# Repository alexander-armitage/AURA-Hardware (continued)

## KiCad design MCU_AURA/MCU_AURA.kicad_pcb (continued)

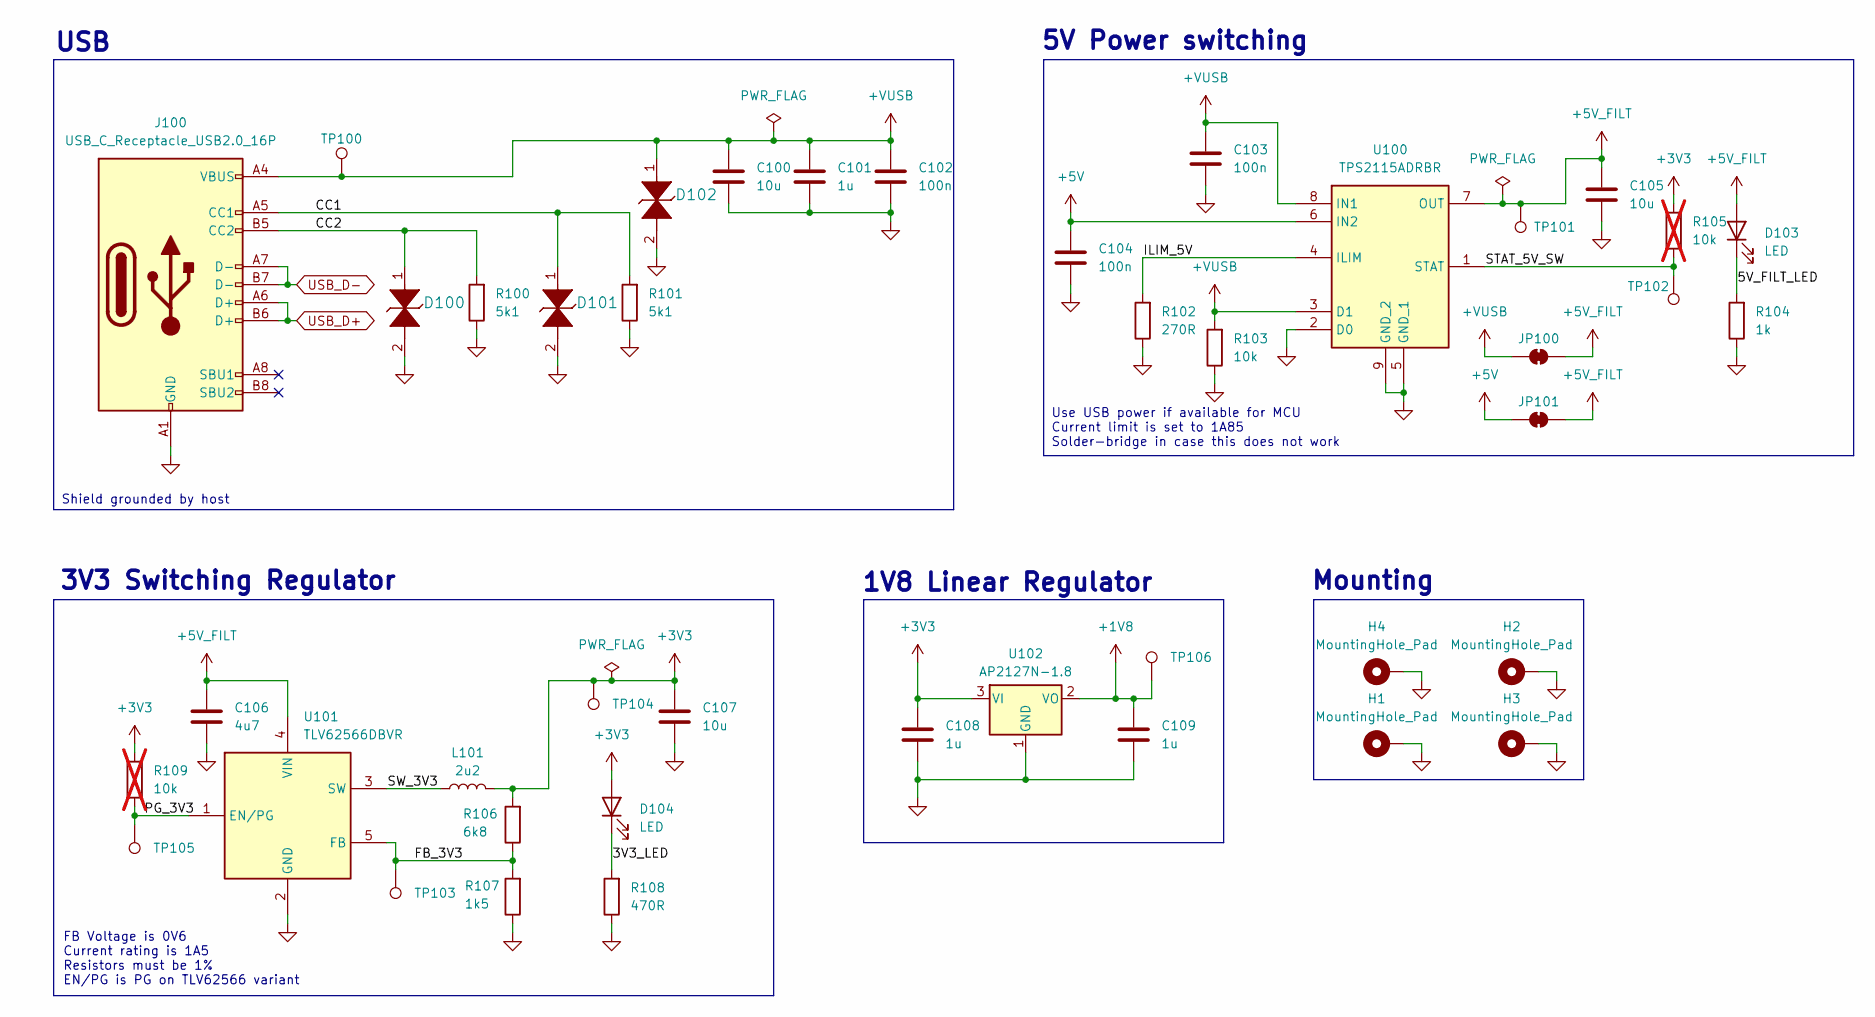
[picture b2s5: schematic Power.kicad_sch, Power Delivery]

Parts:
C100, C105, C107: 10u; C_0402_1005Metric
C101, C108, C109: 1u; C_0402_1005Metric
C102, C103, C104: 100n; C_0402_1005Metric
C106: 4u7; C_0402_1005Metric
D100, D101, D102: TPD1E05U06DPYR; DIO_TPD1E05U06DPYR
D103, D104: LED; LED_0603_1608Metric
H1, H2, H3, H4: MountingHole_Pad; MountingHole_3.2mm_M3_Pad_Via
J100: USB_C_Receptacle_USB2.0_16P; USB_C_Receptacle_GCT_USB4105-xx-A_16P_TopMnt_Horizontal
JP100, JP101: SolderJumper_2_Bridged; SolderJumper-2_P1.3mm_Open_RoundedPad1.0x1.5mm
L101: 2u2; L_1008_2520Metric
R100, R101: 5k1; R_0402_1005Metric
R102: 270R; R_0402_1005Metric
R103: 10k; R_0402_1005Metric
R104: 1k; R_0402_1005Metric
R105, R109: 10k; R_0402_1005Metric; not fitted
R106: 6k8; R_0402_1005Metric
R107: 1k5; R_0402_1005Metric
R108: 470R; R_0402_1005Metric
TP100, TP101, TP102, TP103, TP104, TP105, TP106: TestPoint; TestPoint_Pad_D1.0mm
U100: TPS2115ADRBR; SON65P300X300X100-9N-D; Manufacturer_Part_Number TPS2115ADRBR; Mouser Part Number 595-TPS2115ADRBR
U101: TLV62566DBVR; SOT95P280X145-5N; Manufacturer_Part_Number TLV62566DBVR; Mouser Part Number 595-TLV62566DBVR
U102: AP2127N-1.8; SOT-23

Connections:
+1V8: C109.1, TP106.1, U102.2 (VO); also elsewhere on the board
+3V3: C107.1, C108.1, D104.2 (A), L101.2, R105.2, R106.2, R109.2, TP104.1, U102.3 (VI); also elsewhere on the board
+5V: C104.1, JP101.1 (A), U100.6 (IN2); also elsewhere on the board
+5V_FILT: C105.1, C106.1, D103.2 (A), JP100.2 (B), JP101.2 (B), TP101.1, U100.7 (OUT), U101.4 (VIN); also elsewhere on the board
+VUSB: C100.1, C101.1, C102.1, C103.1, D102.1, J100.A4 (VBUS), J100.A9 (VBUS), J100.B4 (VBUS), J100.B9 (VBUS), JP100.1 (A), R103.2, TP100.1, U100.3 (D1), U100.8 (IN1); also elsewhere on the board
/100_Power/3V3_LED: D104.1 (K), R108.2
/100_Power/5V_FILT_LED: D103.1 (K), R104.2
/100_Power/CC1: D101.1, J100.A5 (CC1), R101.2
/100_Power/CC2: D100.1, J100.B5 (CC2), R100.2
/100_Power/FB_3V3: R106.1, R107.2, TP103.1, U101.5 (FB)
/100_Power/ILIM_5V: R102.2, U100.4 (ILIM)
/100_Power/PG_3V3: R109.1, TP105.1, U101.1 (EN/PG)
/100_Power/STAT_5V_SW: R105.1, TP102.1, U100.1 (STAT)
/100_Power/SW_3V3: L101.1, U101.3 (SW)
GND: C100.2, C101.2, C102.2, C103.2, C104.2, C105.2, C106.2, C107.2, C108.2, C109.2, D100.2, D101.2, D102.2, H1.1, H2.1, H3.1, H4.1, J100.A1 (GND), J100.A12 (GND), J100.B1 (GND), J100.B12 (GND), R100.1, R101.1, R102.1, R103.1, R104.1, R107.1, R108.1, U100.2 (D0), U100.5 (GND_1), U100.9 (GND_2), U101.2 (GND), U102.1 (GND); also elsewhere on the board
USB_D+: J100.A6 (D+), J100.B6 (D+); also elsewhere on the board
USB_D-: J100.A7 (D-), J100.B7 (D-); also elsewhere on the board

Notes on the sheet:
Mounting
Use USB power if available for MCU Current limit is set to 1A85 Solder-bridge in case this does not work
1V8 Linear Regulator
USB
Shield grounded by host
3V3 Switching Regulator
5V Power switching
FB Voltage is 0V6 Current rating is 1A5 Resistors must be 1% EN/PG is PG on TLV62566 variant

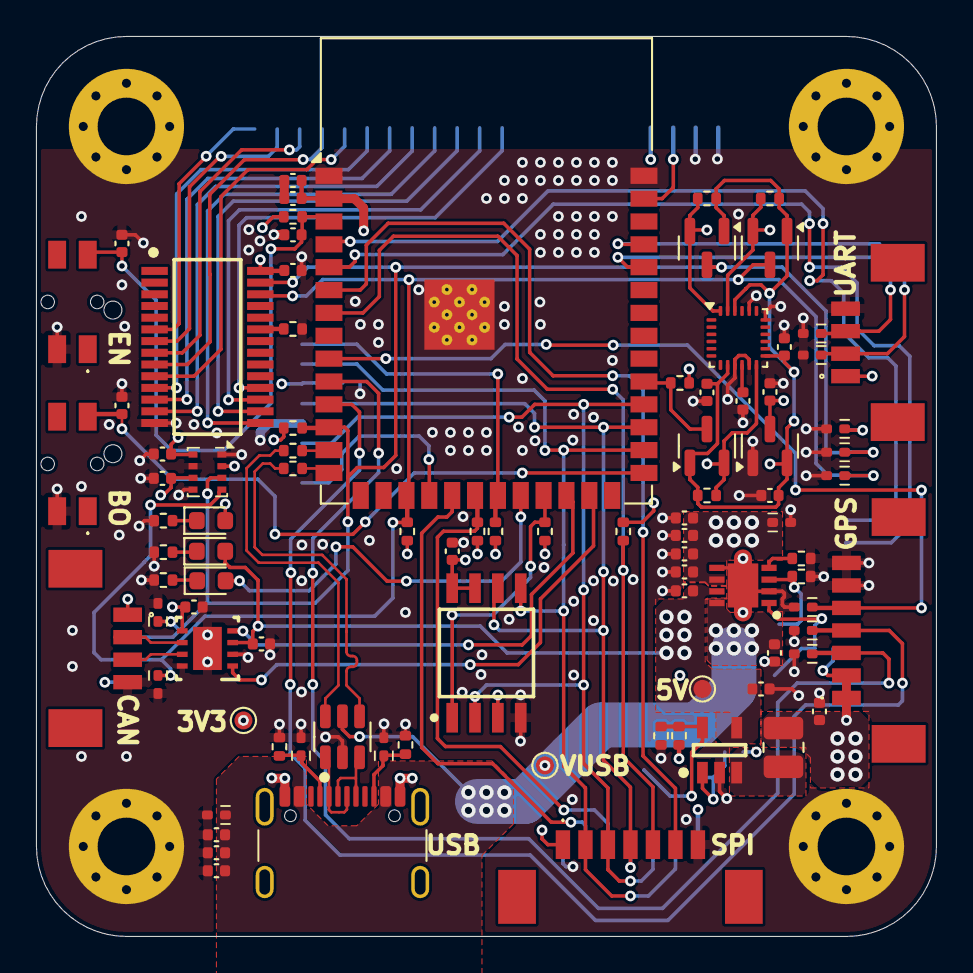
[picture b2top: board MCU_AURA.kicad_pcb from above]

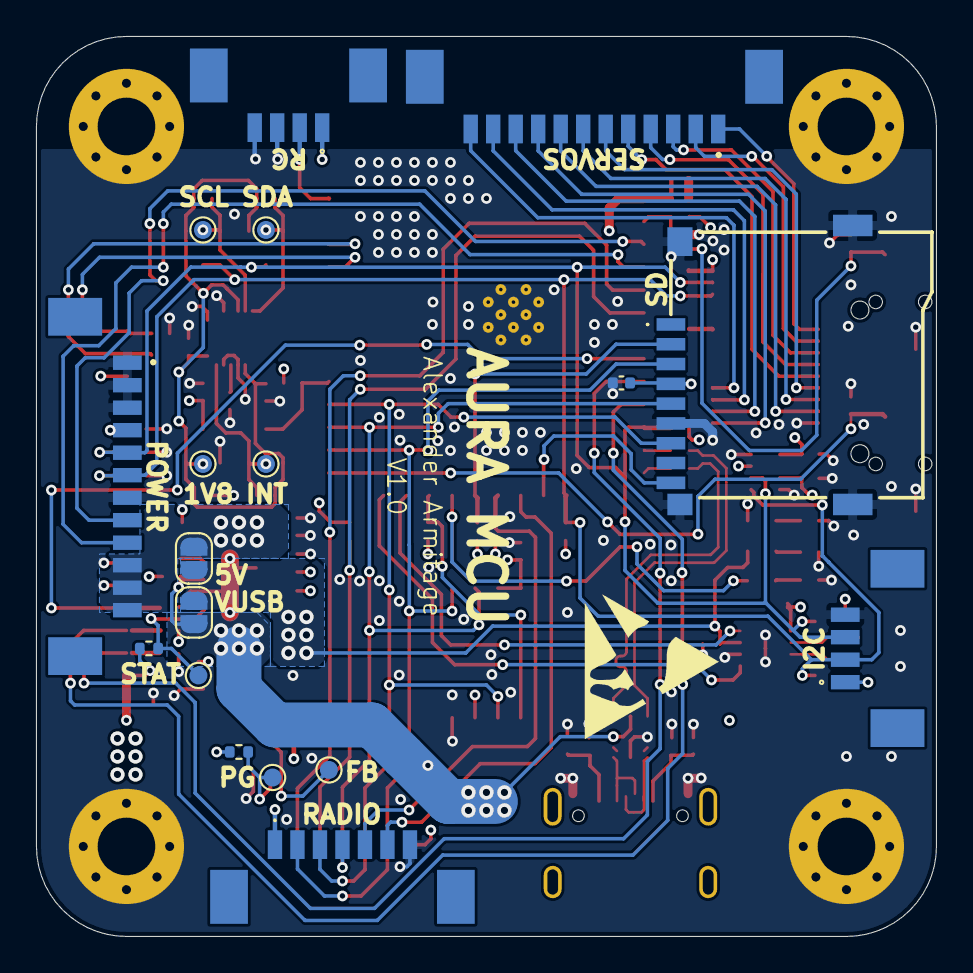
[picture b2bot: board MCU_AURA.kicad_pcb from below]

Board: 4 copper layers, 50.0 x 50.0 mm, 113 parts (18 on the bottom side), 67 nets.

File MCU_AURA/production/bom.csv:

Designator,Footprint,Quantity,Value,LCSC Part #
"C100, C105, C107, C202, C400",0402,5,10u,
"C101, C108, C109, C401",0402,4,1u,
"C102, C103, C104, C201, C203, C204, C300, C301, C302, C303, C304, C305, C306, C402",0402,14,100n,
C106,0805,1,4u7,
C200,0402,1,22u,
"D100, D101, D102, D400, D401, D402, D403, D404, D405, D406, D407, D408, D409, D410",DIO_TPD1E05U06DPYR,14,TPD1E05U06DPYR,
"D103, D104, D300",0603,3,LED,
IC1,SOP65P640X110-28N,1,"PCA9685PW,118",
J1,TFCARDH18,1,TF-CARD_H1.8,
J100,USB_C_Receptacle_GCT_USB4105-xx-A_16P_TopMnt_Horizontal,1,USB_C_Receptacle_USB2.0_16P,
J2,532617003,1,532617003,
J200,TC2050-IDC,1,TC2050-IDC-430,
"J400, J401, J402",532617004,3,532617004,
J403,532617010,1,532617010,
"J404, J405",532617007,2,532617007,
J406,532617012,1,532617012,
J407,CONN_532610000-SD_05_MOL,1,532614005,
L101,1008,1,2u2,
"Q300, Q301, Q302",SOT-23,3,BSS138,
"R1, R2, R201, R202",0402,4,27R,
"R100, R101",0402,2,5k1,
R102,0402,1,270R,
R103,0402,1,220k,
R104,0402,1,4k7,
R106,0402,1,540k,
R107,0402,1,120k,
"R108, R304",0402,2,1k,
"R200, R205, R206, R300, R301, R302, R303, R400, R401",0402,9,10k,
"S200, S201",EVQPUC02K,2,EVQ-PUC02K,
"TP100, TP101, TP102, TP103, TP104, TP105, TP106, TP300, TP301, TP302",TestPoint_Pad_D1.0mm,10,TestPoint,
U100,SON65P300X300X100-9N-D,1,TPS2115ADRBR,
U101,SOT95P280X145-5N,1,TLV62566DBVR,
U102,SOT-23,1,AP2127N-1.8,
U200,ESP32-S3-WROOM-1,1,ESP32-S3-WROOM-1,
U201,SOT-23-6,1,USBLC6-2SC6,
U300,InvenSense_QFN-24_3x3mm_P0.4mm,1,ICM-20948,
U301,Bosch_LGA-8_2x2.5mm_P0.65mm_ClockwisePinNumbering,1,BMP280,

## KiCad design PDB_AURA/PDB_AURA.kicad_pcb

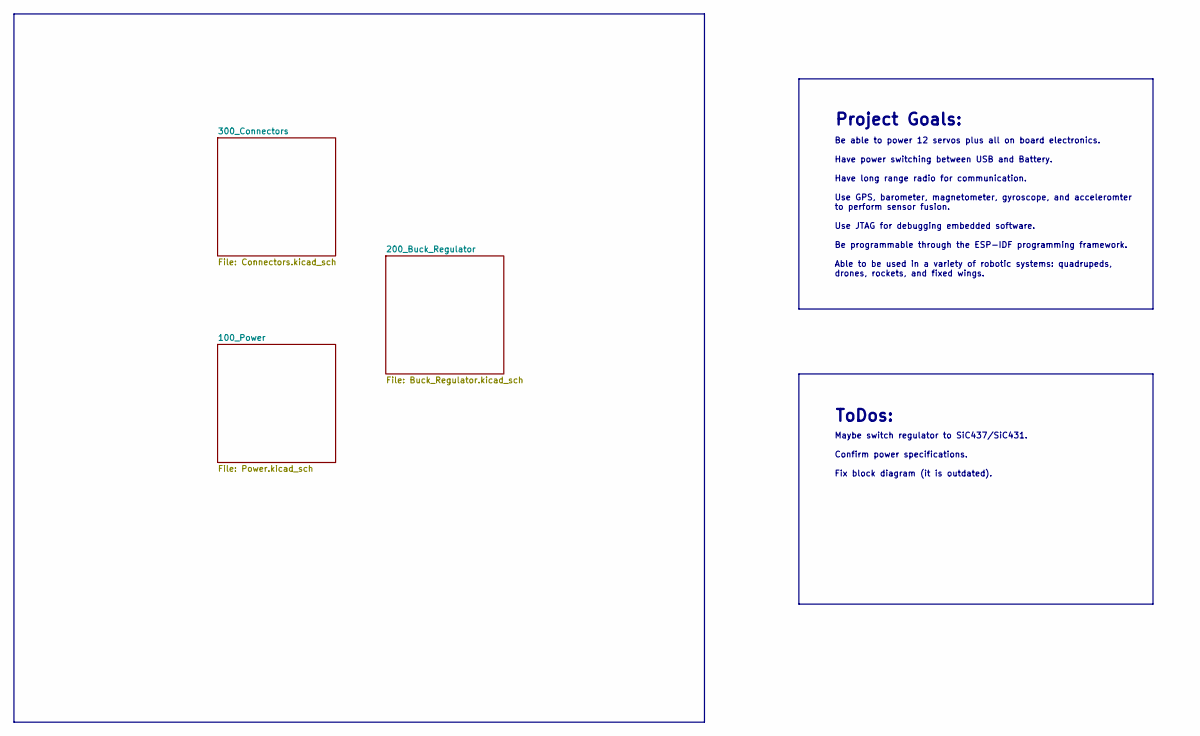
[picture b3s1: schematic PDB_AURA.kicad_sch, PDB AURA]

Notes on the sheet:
ToDos:
Be able to power 12 servos plus all on board electronics. Have power switching between USB and Battery. Have long range radio for communication. Use GPS, barometer, magnetometer, gyroscope, and acceleromter to perform sensor fusion. Use JTAG for debugging embedded software. Be programmable through 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
Maybe switch regulator to SiC437/SiC431. Confirm power specifications. Fix block diagram (it is outdated).
Project Goals:

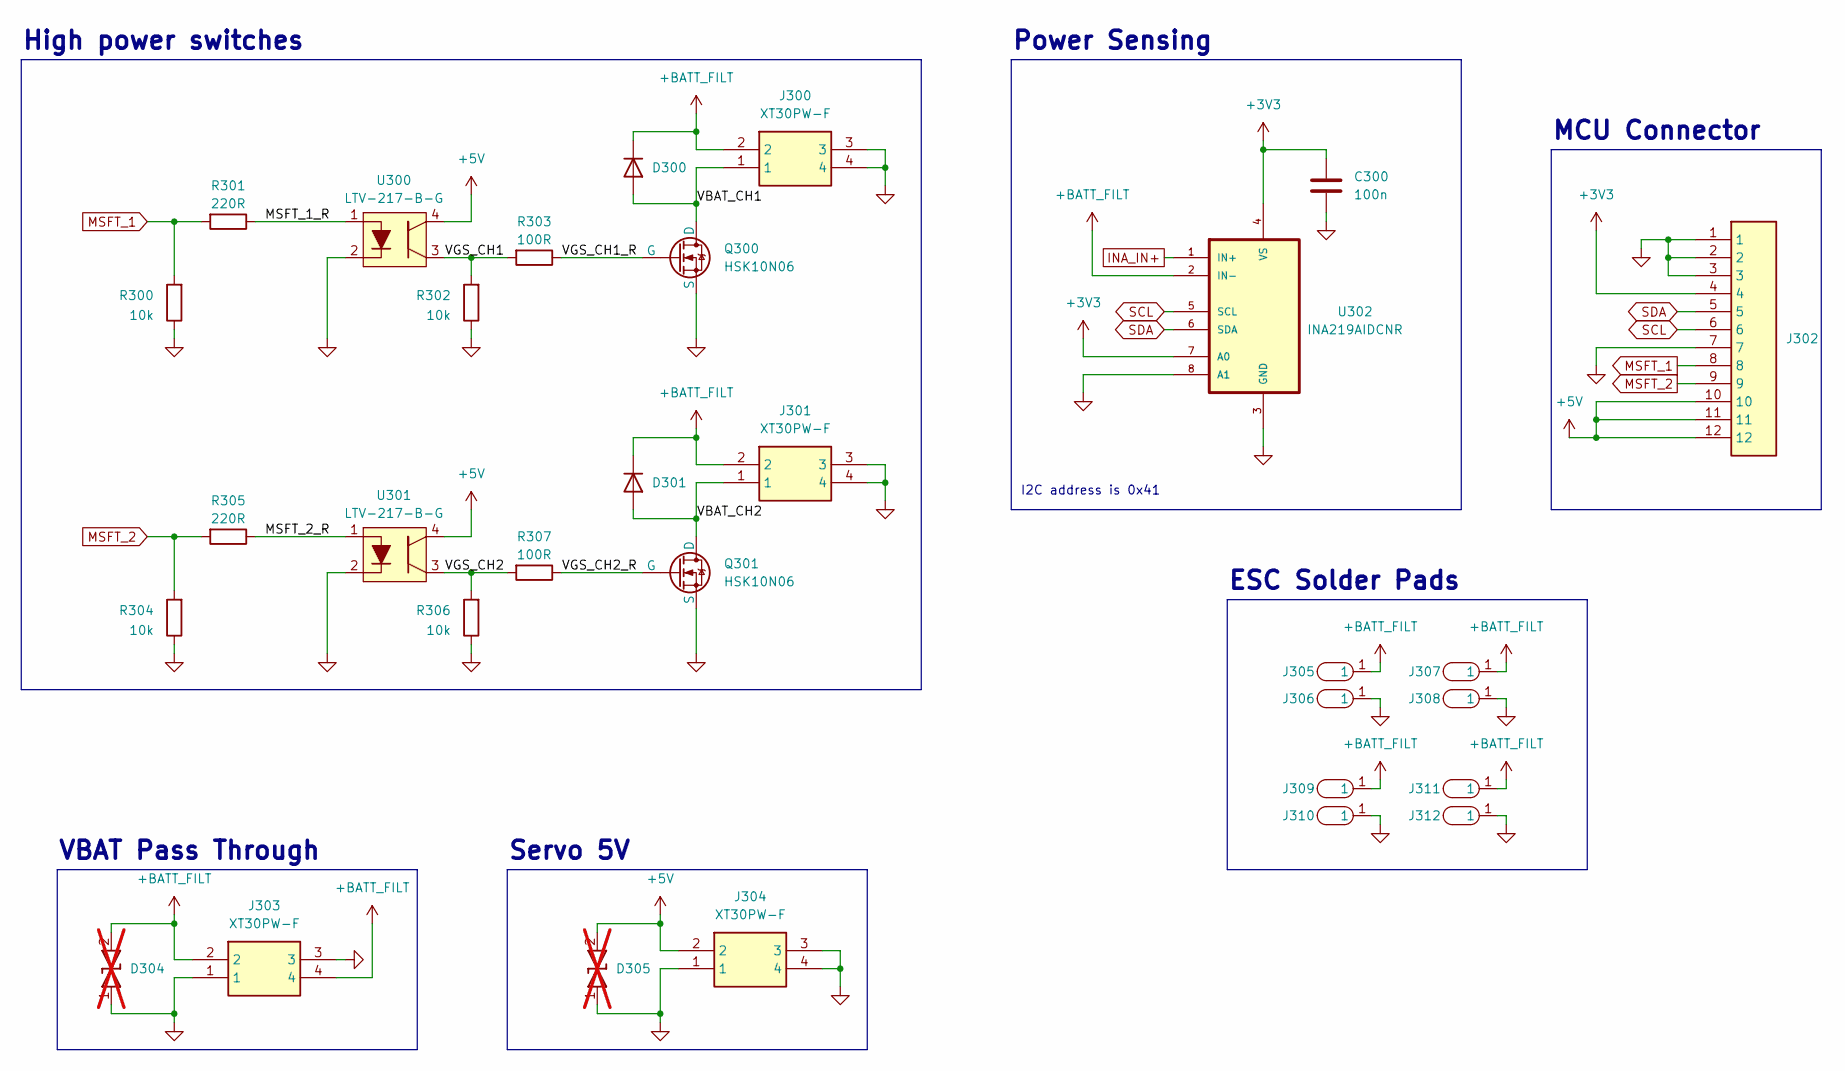
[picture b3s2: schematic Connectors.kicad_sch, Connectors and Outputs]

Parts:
C300: 100n; C_0402_1005Metric
D300, D301: SBR3M30P17
D304, D305: SMBJ33CA; DIONM5436X244N; Manufacturer_Part_Number SMBJ33CA; Mouser Part Number 78-SMBJ33CA; not fitted
J300, J301, J303, J304: XT30PW-F; XT30PWF; Manufacturer_Part_Number XT30PW-F
J302: 532617012; 53261-1271; Manufacturer_Part_Number 532617012
J305, J306, J307, J308, J309, J310, J311, J312: PWR_SOLDER_PAD
Q300, Q301: HSK10N06
R300, R302, R304, R306: 10k; R_0402_1005Metric
R301, R305: 220R; R_0402_1005Metric
R303, R307: 100R; R_0402_1005Metric
U300, U301: LTV-217-B-G; SOIC127P700X210-4N
U302: INA219AIDCNR; SOT65P280X145-8N

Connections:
+3V3: C300.1, J302.4, U302.4 (VS), U302.7 (A0)
+5V: D305.2, J302.10, J302.11, J302.12, J304.2, U300.4, U301.4; also elsewhere on the board
+BATT_FILT: D300.1 (K), D301.1 (K), D304.2, J300.2, J301.2, J303.2, J303.4, J305.1, J307.1, J309.1, J311.1, U302.2 (IN-); also elsewhere on the board
/300_Connectors/MSFT_1_R: R301.1, U300.1
/300_Connectors/MSFT_2_R: R305.1, U301.1
/300_Connectors/VBAT_CH1: D300.2 (A), J300.1, Q300.2 (D)
/300_Connectors/VBAT_CH2: D301.2 (A), J301.1, Q301.2 (D)
/300_Connectors/VGS_CH1: R302.2, R303.2, U300.3
/300_Connectors/VGS_CH1_R: Q300.1 (G), R303.1
/300_Connectors/VGS_CH2: R306.2, R307.2, U301.3
/300_Connectors/VGS_CH2_R: Q301.1 (G), R307.1
GND: C300.2, D304.1, D305.1, J300.3, J300.4, J301.3, J301.4, J302.1, J302.2, J302.3, J302.7, J303.1, J303.3, J304.1, J304.3, J304.4, J306.1, J308.1, J310.1, J312.1, Q300.3 (S), Q301.3 (S), R300.1, R302.1, R304.1, R306.1, U300.2, U301.2, U302.3 (GND), U302.8 (A1); also elsewhere on the board
INA_IN+: U302.1 (IN+); also elsewhere on the board
MSFT_1: J302.8, R300.2, R301.2
MSFT_2: J302.9, R304.2, R305.2
SCL: J302.6, U302.5 (SCL)
SDA: J302.5, U302.6 (SDA)

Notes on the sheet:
Servo 5V
MCU Connector
High power switches
VBAT Pass Through
Power Sensing
I2C address is 0x41
ESC Solder Pads

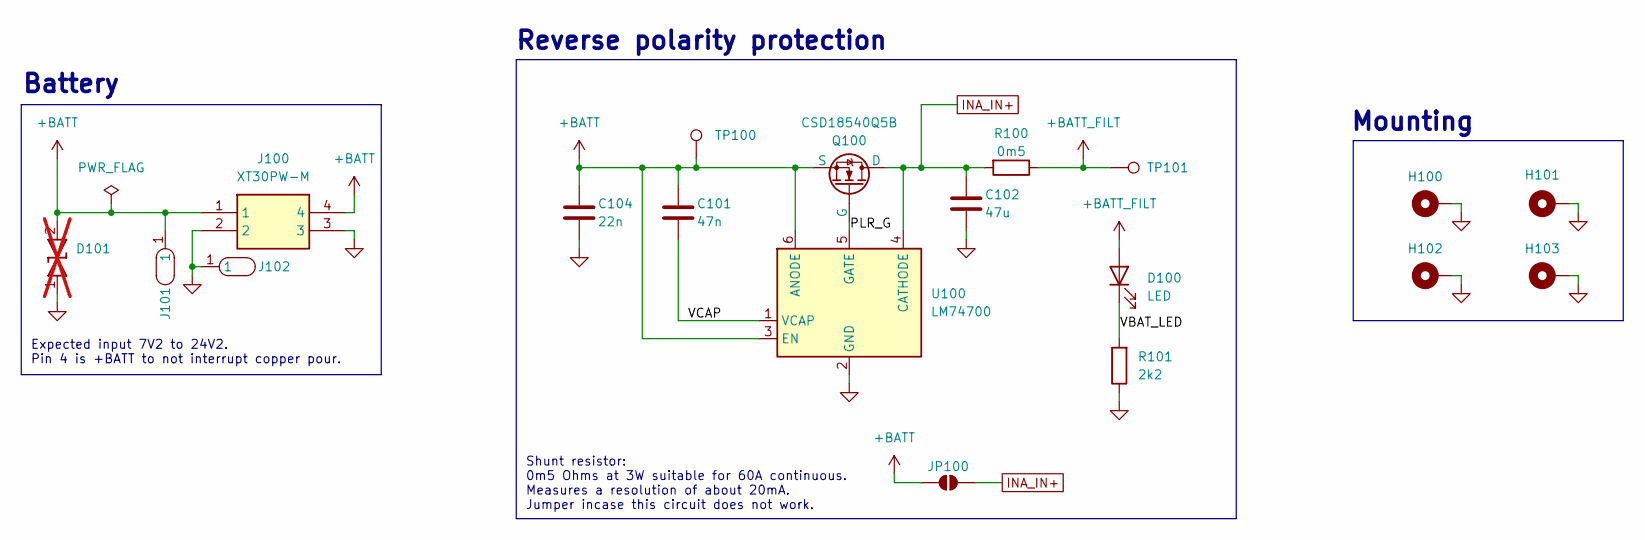
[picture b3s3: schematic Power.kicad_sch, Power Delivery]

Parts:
C101: 47n; C_0402_1005Metric
C102: 47u; C_1210_3225Metric
C104: 22n; C_0402_1005Metric
D100: LED; LED_0603_1608Metric
D101: SMBJ33CA; DIONM5436X244N; Manufacturer_Part_Number SMBJ33CA; Mouser Part Number 78-SMBJ33CA; not fitted
H100, H101, H102, H103: MountingHole_Pad; MountingHole_3.2mm_M3_Pad_Via
J100: XT30PW-M; XT30PWM; Manufacturer_Part_Number XT30PW-M
J101, J102: BAT_SOLDER_PAD
JP100: SolderJumper_2_Open; SolderJumper-2_P1.3mm_Open_RoundedPad1.0x1.5mm
Q100: CSD18540Q5B
R100: 0m5; R_2512_6332Metric
R101: 2k2; R_0402_1005Metric
TP100, TP101: TestPoint; TestPoint_Pad_D1.0mm
U100: LM74700; SOT-23-6

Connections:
+BATT: C101.1, C104.1, D101.2, J100.1, J100.4, J101.1, JP100.1 (A), Q100.3 (S), TP100.1, U100.3 (EN), U100.6 (ANODE)
+BATT_FILT: D100.2 (A), R100.1, TP101.1; also elsewhere on the board
/100_Power/PLR_G: Q100.1 (G), U100.5 (GATE)
/100_Power/VBAT_LED: D100.1 (K), R101.2
/100_Power/VCAP: C101.2, U100.1 (VCAP)
GND: C102.2, C104.2, D101.1, H100.1, H101.1, H102.1, H103.1, J100.2, J100.3, J102.1, R101.1, U100.2 (GND); also elsewhere on the board
INA_IN+: C102.1, JP100.2 (B), Q100.2 (D), R100.2, U100.4 (CATHODE); also elsewhere on the board

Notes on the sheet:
Mounting
Battery
Reverse polarity protection
Expected input 7V2 to 24V2. Pin 4 is +BATT to not interrupt copper pour.
Shunt resistor: 0m5 Ohms at 3W suitable for 60A continuous. Measures a resolution of about 20mA. Jumper incase this circuit does not work.

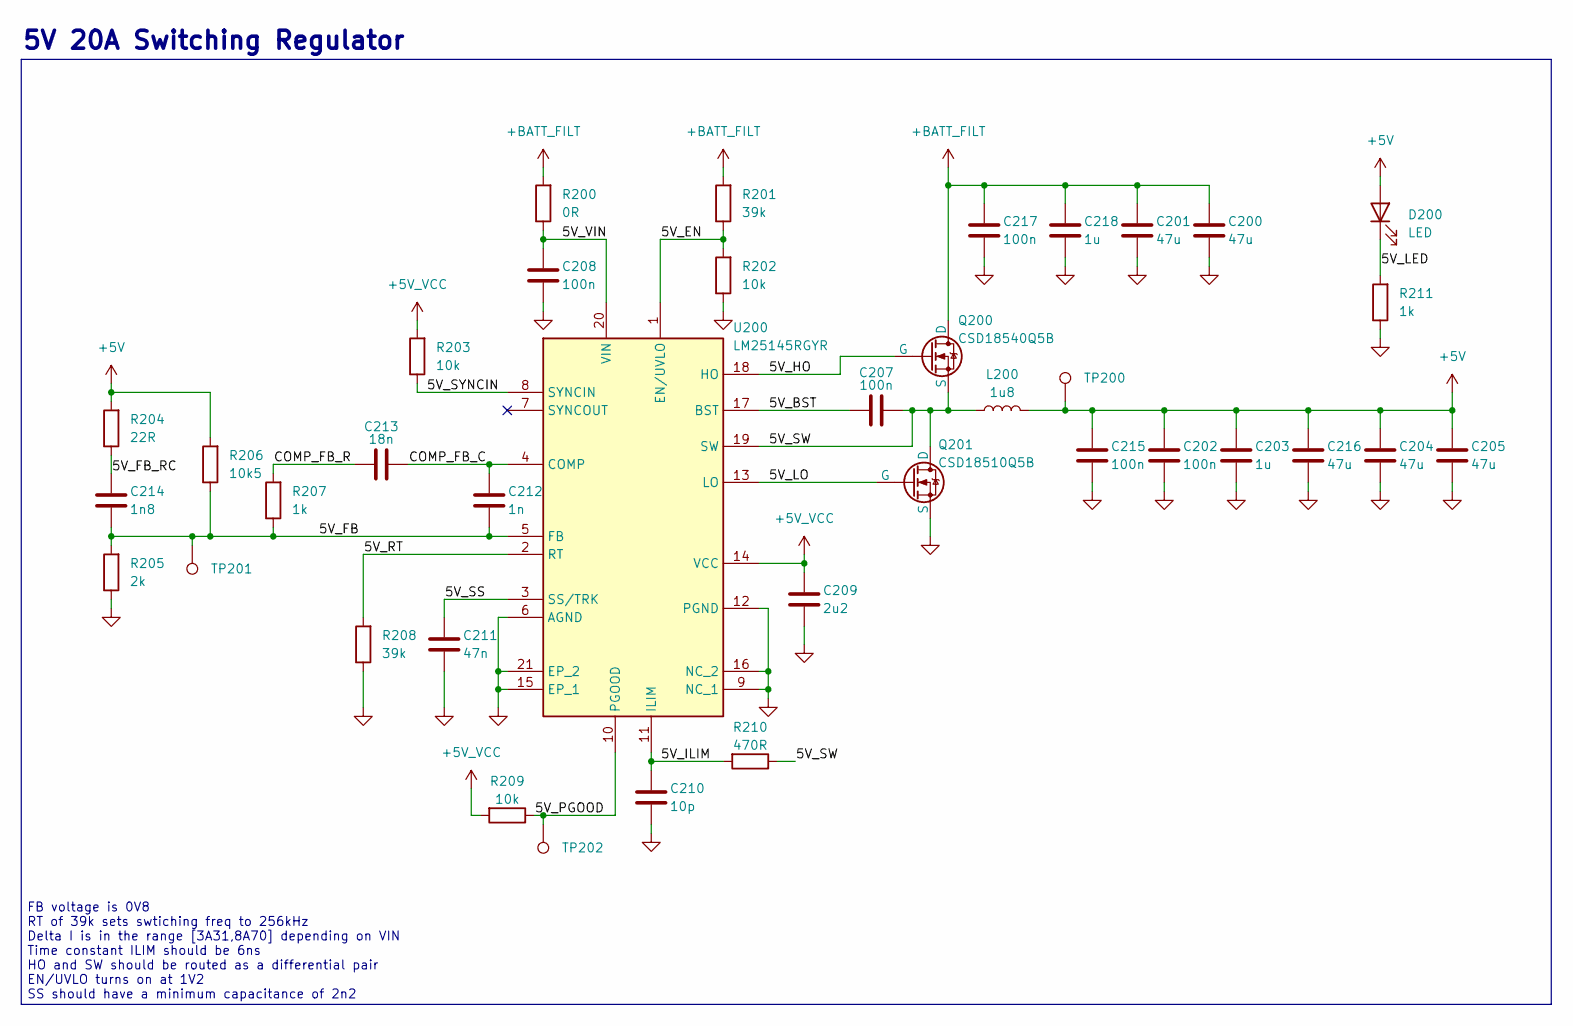
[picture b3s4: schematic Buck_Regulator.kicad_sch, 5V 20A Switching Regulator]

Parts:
C200, C201, C204, C205, C216: 47u; C_1210_3225Metric
C202, C207, C208, C215, C217: 100n; C_0402_1005Metric
C203, C218: 1u; C_0402_1005Metric
C209: 2u2; C_0402_1005Metric
C210: 10p; C_0402_1005Metric
C211: 47n; C_0402_1005Metric
C212: 1n; C_0402_1005Metric
C213: 18n; C_0402_1005Metric
C214: 1n8; C_0402_1005Metric
D200: LED; LED_0603_1608Metric
L200: 1u8; Untitled
Q200: CSD18540Q5B
Q201: CSD18510Q5B; CSD18540Q5BT
R200: 0R; R_0402_1005Metric; JLCPCB C25783
R201, R208: 39k; R_0402_1005Metric; JLCPCB C25783
R202, R203, R209: 10k; R_0402_1005Metric
R204: 22R; R_0402_1005Metric
R205: 2k; R_0402_1005Metric
R206: 10k5; R_0402_1005Metric
R207, R211: 1k; R_0402_1005Metric
R210: 470R; R_0402_1005Metric; JLCPCB C25091
TP200, TP201, TP202: TestPoint; TestPoint_Pad_D1.0mm
U200: LM25145RGYR; RGY0020B; Manufacturer_Part_Number LM25145RGYR; Mouser Part Number 595-LM25145RGYR

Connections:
+5V: C202.1, C203.1, C204.1, C205.1, C215.1, C216.1, D200.2 (A), L200.2, R204.2, R206.2, TP200.1; also elsewhere on the board
+5V_VCC: C209.1, R203.2, R209.2, U200.14 (VCC)
+BATT_FILT: C200.1, C201.1, C217.1, C218.1, Q200.2 (D), R200.2, R201.2; also elsewhere on the board
/200_Buck_Regulator/5V_BST: C207.1, U200.17 (BST)
/200_Buck_Regulator/5V_EN: R201.1, R202.2, U200.1 (EN/UVLO)
/200_Buck_Regulator/5V_FB: C212.2, C214.2, R205.2, R206.1, R207.1, TP201.1, U200.5 (FB)
/200_Buck_Regulator/5V_FB_RC: C214.1, R204.1
/200_Buck_Regulator/5V_HO: Q200.1 (G), U200.18 (HO)
/200_Buck_Regulator/5V_ILIM: C210.1, R210.2, U200.11 (ILIM)
/200_Buck_Regulator/5V_LED: D200.1 (K), R211.2
/200_Buck_Regulator/5V_LO: Q201.1 (G), U200.13 (LO)
/200_Buck_Regulator/5V_PGOOD: R209.1, TP202.1, U200.10 (PGOOD)
/200_Buck_Regulator/5V_RT: R208.2, U200.2 (RT)
/200_Buck_Regulator/5V_SS: C211.1, U200.3 (SS/TRK)
/200_Buck_Regulator/5V_SW: C207.2, L200.1, Q200.3 (S), Q201.2 (D), R210.1, U200.19 (SW)
/200_Buck_Regulator/5V_SYNCIN: R203.1, U200.8 (SYNCIN)
/200_Buck_Regulator/5V_VIN: C208.1, R200.1, U200.20 (VIN)
/200_Buck_Regulator/COMP_FB_C: C212.1, C213.2, U200.4 (COMP)
/200_Buck_Regulator/COMP_FB_R: C213.1, R207.2
GND: C200.2, C201.2, C202.2, C203.2, C204.2, C205.2, C208.2, C209.2, C210.2, C211.2, C215.2, C216.2, C217.2, C218.2, Q201.3 (S), R202.1, R205.1, R208.1, R211.1, U200.6 (AGND), U200.9 (NC_1), U200.12 (PGND), U200.15 (EP_1), U200.16 (NC_2), U200.21 (EP_2); also elsewhere on the board

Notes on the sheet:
FB voltage is 0V8 RT of 39k sets swtiching freq to 256kHz Delta I is in the range [3A31,8A70] depending on VIN Time constant ILIM should be 6ns HO and SW should be routed as a differential pair EN/UVLO turns on at 1V2 SS should have a minimum capacitance of 2n2
5V 20A Switching Regulator

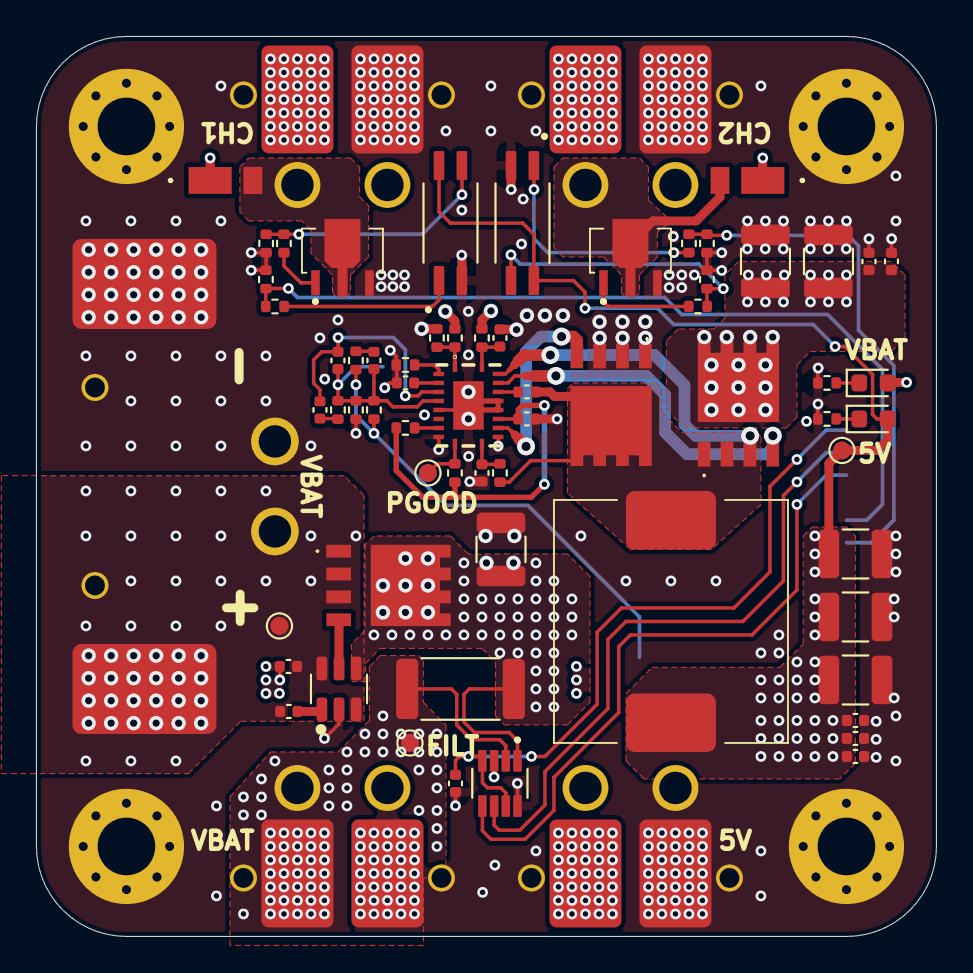
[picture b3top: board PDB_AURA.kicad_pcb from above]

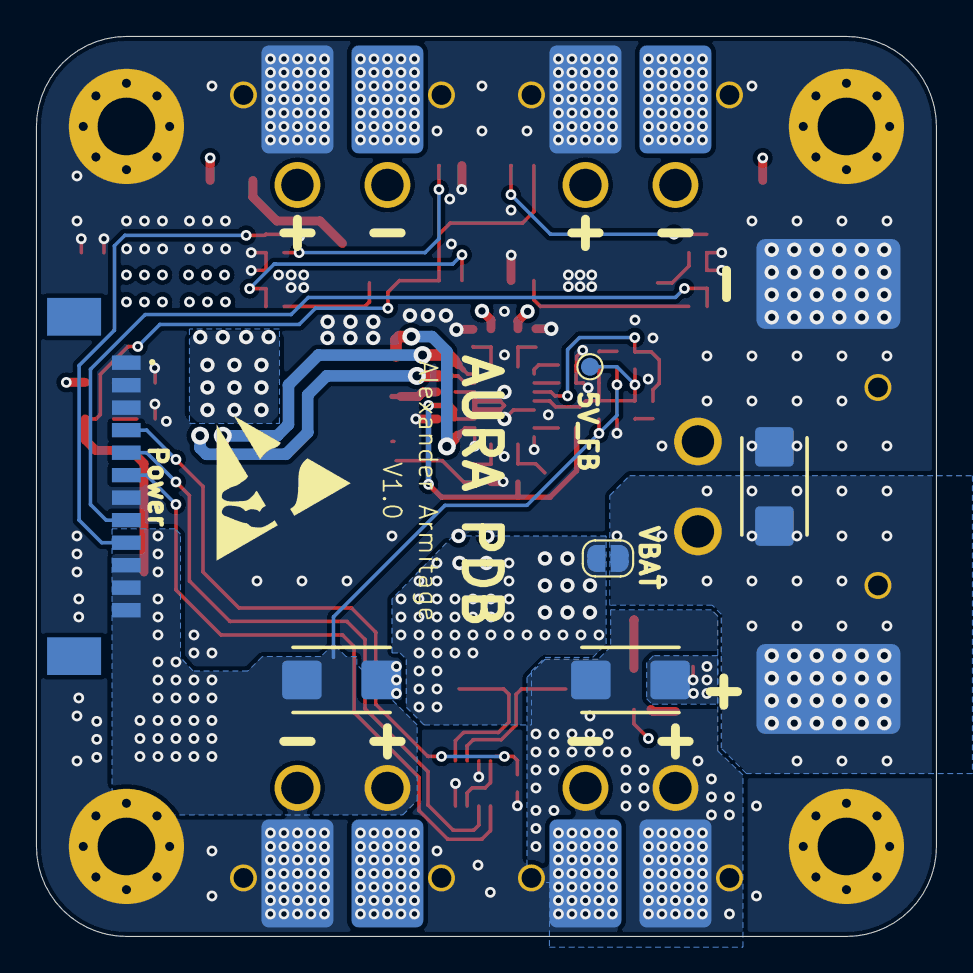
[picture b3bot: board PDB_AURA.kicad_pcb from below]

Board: 4 copper layers, 50.0 x 50.0 mm, 88 parts (14 on the bottom side), 38 nets.

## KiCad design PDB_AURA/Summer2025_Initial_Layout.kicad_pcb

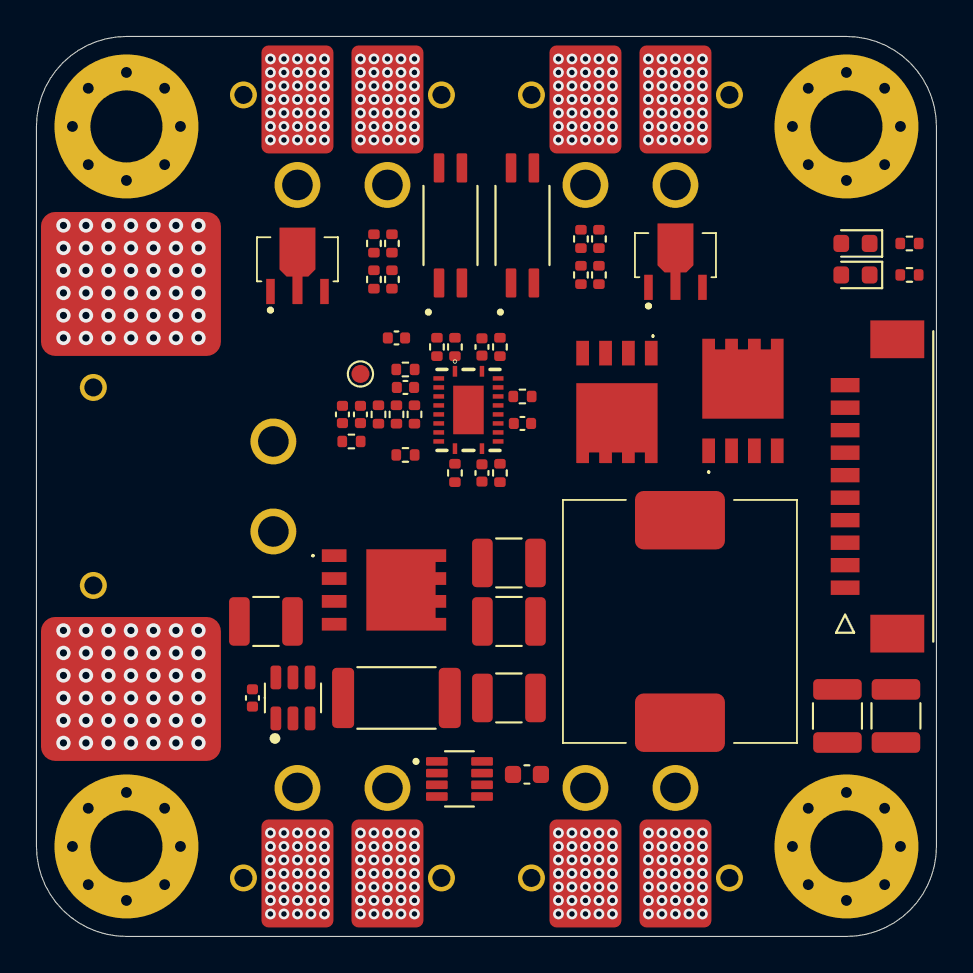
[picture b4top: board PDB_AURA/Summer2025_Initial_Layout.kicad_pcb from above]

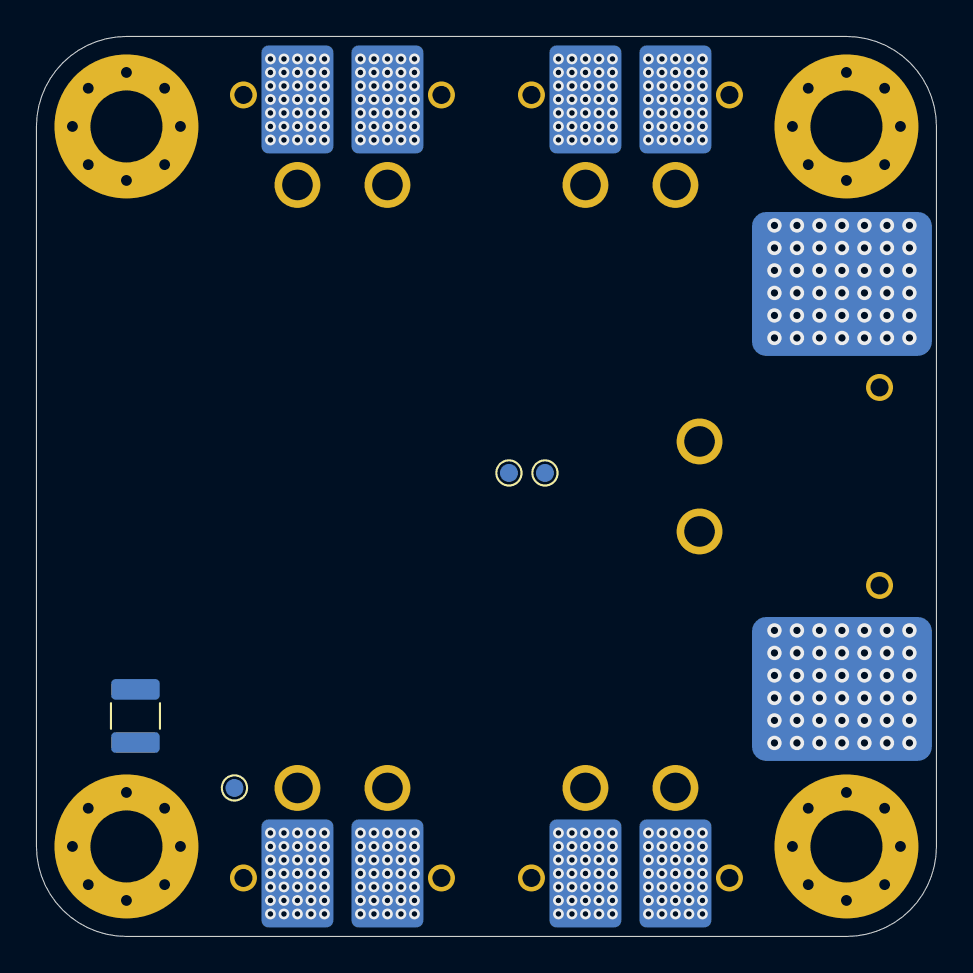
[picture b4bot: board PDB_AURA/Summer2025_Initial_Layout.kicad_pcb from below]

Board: 4 copper layers, 50.0 x 50.0 mm, 76 parts (12 on the bottom side), 38 nets, no tracks yet.

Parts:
C1: 1n; C_0402_1005Metric
C2: 8n2; C_0402_1005Metric
C3, C8: 100n; C_0402_1005Metric
C4, C4#2: 390p; C_0402_1005Metric
C5: 100n; R_0402_1005Metric
C6: 2u2; C_0402_1005Metric
C7: 10p; C_0402_1005Metric
C9, C11, C12, C14, C15, C16: 22u; C_1210_3225Metric
C10: 47u; C_1210_3225Metric
C200: 100n; C_0603_1608Metric
D1, D101: LED; LED_0603_1608Metric
H1, H2, H3, H4: MountingHole_Pad; MountingHole_4mm_Pad_Via
J1, J2, J3, J4, J5, J6, J7, J8: PWR_SOLDER_PAD
J9, J10: BAT_SOLDER_PAD
J100: XT30PW-M; XT30PWM
J200: 532617010
J201, J202, J203, J204: XT30PW-F; XT30PWF
L1: 1u8; Untitled
Q1, Q3: CSD18540Q5B
Q2: CSD18510Q5B; CSD18540Q5BT
Q200, Q201: HSK10N06
R1: 18k; R_0402_1005Metric
R2: 3k4; R_0402_1005Metric
R3: 1k47; R_0402_1005Metric
R4, R8, R13, R112: 4k7; R_0402_1005Metric
R5: 249R; R_0402_1005Metric
R6: 20k; R_0402_1005Metric
R7: 576R; R_0402_1005Metric
R9: 35k7; R_0402_1005Metric
R10: 9k1; R_0402_1005Metric
R11: 2R1; R_0402_1005Metric
R12: 0m5; R_2512_6332Metric
R200, R202, R204, R206: 10k; R_0402_1005Metric
R201, R205: 470R; R_0402_1005Metric
R203, R207: 100R; R_0402_1005Metric
TP1, TP2, TP3, TP4: TestPoint; TestPoint_Pad_D1.0mm
U1: LM25145RGYR; RGY0020B
U2: LM74700; SOT-23-6
U200, U201: LTV-217-B-G; SOIC127P700X210-4N
U202: INA219AIDCNR; SOT65P280X145-8N

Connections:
+3V3: C200.1, J200.3, U202.4 (VS), U202.7 (A0)
+5V: C9.1, C14.1, C15.1, D1.2 (A), J200.1, J200.2, J204.1, L1.2, R1.2, R5.2, TP4.1, U200.4, U201.4
+5V_VCC: C6.1, R6.2, R8.2, U1.14 (VCC)
+BATT: C12.1, J9.1, J100.1, Q3.3 (S), U2.3 (EN), U2.6 (ANODE)
+BATT_FILT: C10.1, D101.2 (A), J1.1, J3.1, J5.1, J7.1, J201.1, J202.1, J203.1, Q1.2 (D), R9.2, R11.2, R12.1, U202.2 (IN-)
/100_Power/5V_BST: C5.1, U1.17 (BST)
/100_Power/5V_EN: R9.1, R10.2, U1.1 (EN/UVLO)
/100_Power/5V_FB: C1.2, C4.2, R1.1, R2.2, R3.1, TP2.1, U1.5 (FB)
/100_Power/5V_FB_RC: C4.1, R5.1
/100_Power/5V_HO: Q1.1 (G), U1.18 (HO)
/100_Power/5V_ILIM: C7.1, R7.2, U1.11 (ILIM)
/100_Power/5V_LED: D1.1 (K), R13.2
/100_Power/5V_LO: Q2.1 (G), U1.13 (LO)
/100_Power/5V_PGOOD: R8.1, TP3.1, U1.10 (PGOOD)
/100_Power/5V_RT: R4.2, U1.2 (RT)
/100_Power/5V_SS: C3.1, U1.3 (SS/TRK)
/100_Power/5V_SW: C5.2, L1.1, Q1.3 (S), Q2.2 (D), R7.1, U1.19 (SW)
/100_Power/5V_SYNCIN: R6.1, U1.8 (SYNCIN)
/100_Power/5V_SYNCOUT: TP1.1, U1.7 (SYNCOUT)
/100_Power/5V_VIN: C8.1, R11.1, U1.20 (VIN)
/100_Power/COMP_FB_C: C1.1, C2.2, U1.4 (COMP)
/100_Power/COMP_FB_R: C2.1, R3.2
/100_Power/PLR_G: Q3.1 (G), U2.5 (GATE)
/100_Power/VBAT_LED: D101.1 (K), R112.2
/200_Connectors/MSFT_1_R: R201.1, U200.1
/200_Connectors/MSFT_2_R: R205.1, U201.1
/200_Connectors/VBAT_CH1: J201.2, Q200.2 (D)
/200_Connectors/VBAT_CH2: J202.2, Q201.2 (D)
/200_Connectors/VGS_CH1: R202.2, R203.2, U200.3
/200_Connectors/VGS_CH1_R: Q200.1 (G), R203.1
/200_Connectors/VGS_CH2: R206.2, R207.2, U201.3
/200_Connectors/VGS_CH2_R: Q201.1 (G), R207.1
GND: C3.2, C6.2, C7.2, C8.2, C9.2, C10.2, C11.2, C12.2, C14.2, C15.2, C16.2, C200.2, J2.1, J4.1, J6.1, J8.1, J10.1, J100.2, J100.3, J100.4, J200.6, J200.9, J200.10, J201.3, J201.4, J202.3, J202.4, J203.2, J203.3, J203.4, J204.2, J204.3, J204.4, Q2.3 (S), Q200.3 (S), Q201.3 (S), R2.1, R4.1, R10.1, R13.1, R112.1, R200.1, R202.1, R204.1, R206.1, U1.6 (AGND), U1.9 (NC_1), U1.12 (PGND), U1.15 (EP_1), U1.16 (NC_2), U1.21 (EP_2), U2.2 (GND), U200.2, U201.2, U202.3 (GND), U202.8 (A1)
INA_IN+: C11.1, C16.1, Q3.2 (D), R12.2, U2.4 (CATHODE), U202.1 (IN+)
MSFT_1: J200.7, R200.2, R201.2
MSFT_2: J200.8, R204.2, R205.2
SCL: J200.4, U202.5 (SCL)
SDA: J200.5, U202.6 (SDA)
